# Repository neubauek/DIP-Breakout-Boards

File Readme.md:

# SMT to DIP Breakout Boards

Breakout boards to convert SMT chips to DIP format for use in breadboard prototyping.

These designs have all been validated against DirtyPCBs and OSHPark design rules, but most have not been panelized and sent off to be fabricated.

Be mindful of sizing when using QFN components. I noticed when developing my QFN-28 board that not all QFN-28 chips are created with equal footprints.

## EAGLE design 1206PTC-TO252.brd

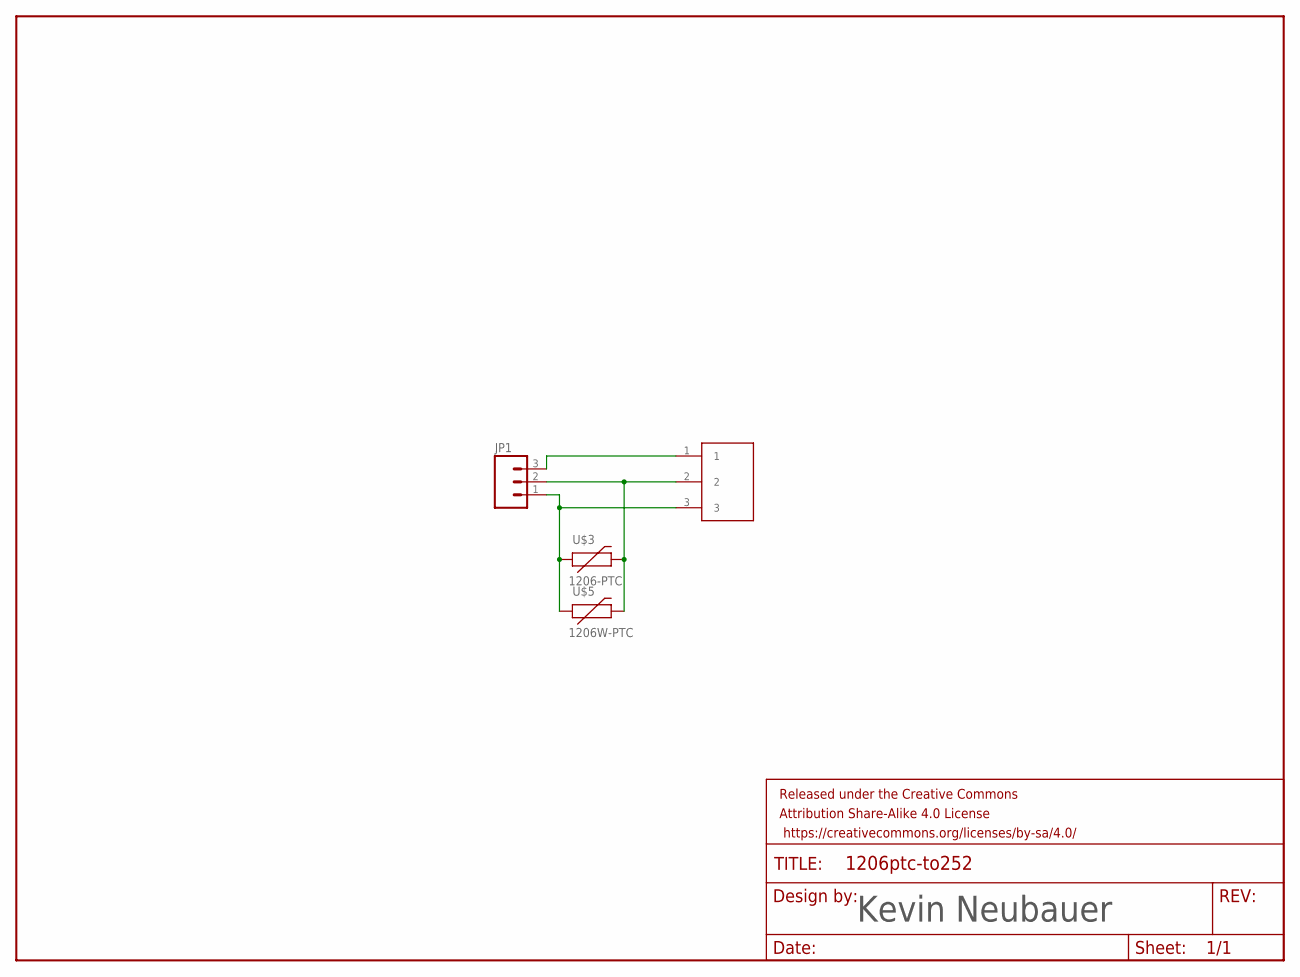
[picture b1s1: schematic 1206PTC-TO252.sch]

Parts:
FRAME1: FRAME-LETTER; CREATIVE_COMMONS
JP1: M03PTH; 1X03
U$3: 1206-PTC; PTC-1206
U$4: DPAK
U$5: 1206W-PTC; PTC-1206-WIDE

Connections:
unnamed: JP1.1, U$3.1, U$4.3, U$5.1
unnamed: JP1.2, U$3.2, U$4.2, U$5.2
unnamed: JP1.3, U$4.1

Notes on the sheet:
Kevin Neubauer

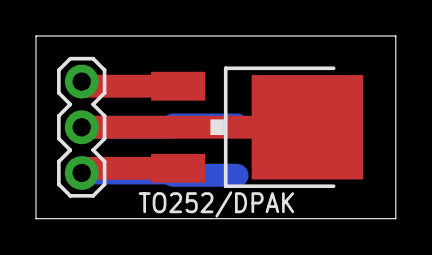
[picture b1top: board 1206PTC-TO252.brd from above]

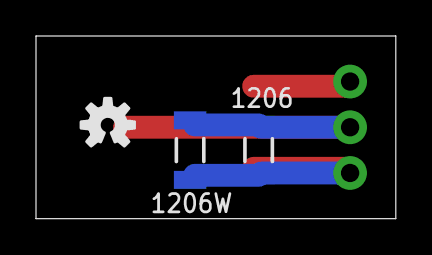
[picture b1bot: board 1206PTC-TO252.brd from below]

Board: 2 copper layers, 20.0 x 10.2 mm, 6 parts (3 on the bottom side), 3 nets.

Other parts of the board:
U$2: OSHW-LOGO-S

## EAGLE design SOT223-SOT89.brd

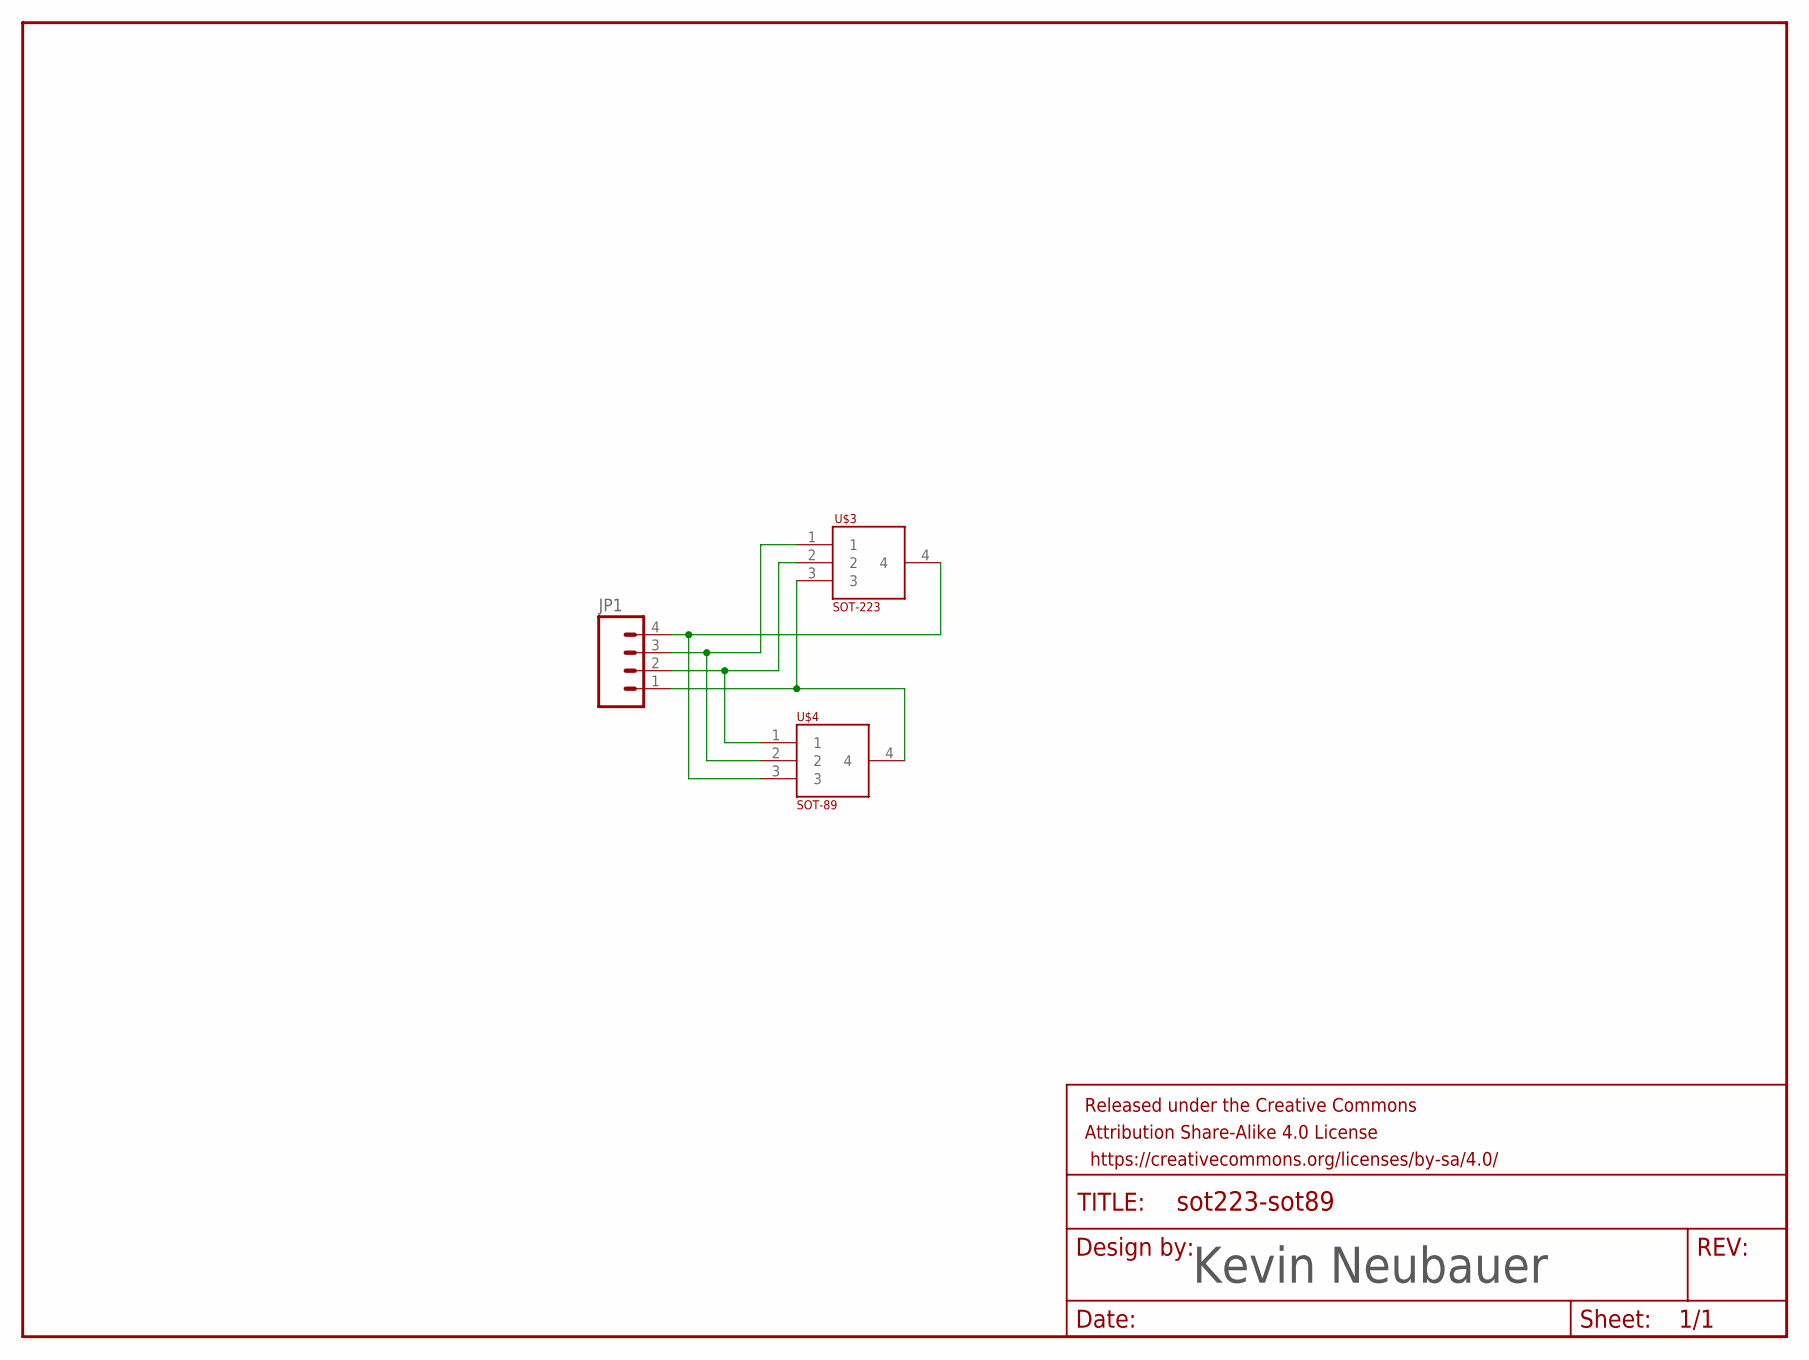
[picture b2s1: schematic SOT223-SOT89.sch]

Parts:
FRAME1: FRAME-LETTER; CREATIVE_COMMONS
JP1: M04PTH; 1X04
U$3: SOT-223
U$4: SOT-89

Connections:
unnamed: JP1.2, U$3.2, U$4.1
unnamed: JP1.3, U$3.1, U$4.2
unnamed: JP1.1, U$3.3, U$4.4
unnamed: JP1.4, U$3.4, U$4.3

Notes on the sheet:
Kevin Neubauer

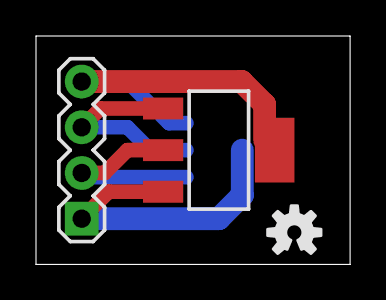
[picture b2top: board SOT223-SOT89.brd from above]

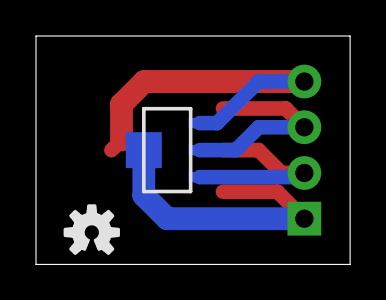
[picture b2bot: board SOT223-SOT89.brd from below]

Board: 2 copper layers, 17.5 x 12.7 mm, 6 parts (2 on the bottom side), 4 nets.

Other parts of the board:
U$1, U$2: OSHW-LOGO-S

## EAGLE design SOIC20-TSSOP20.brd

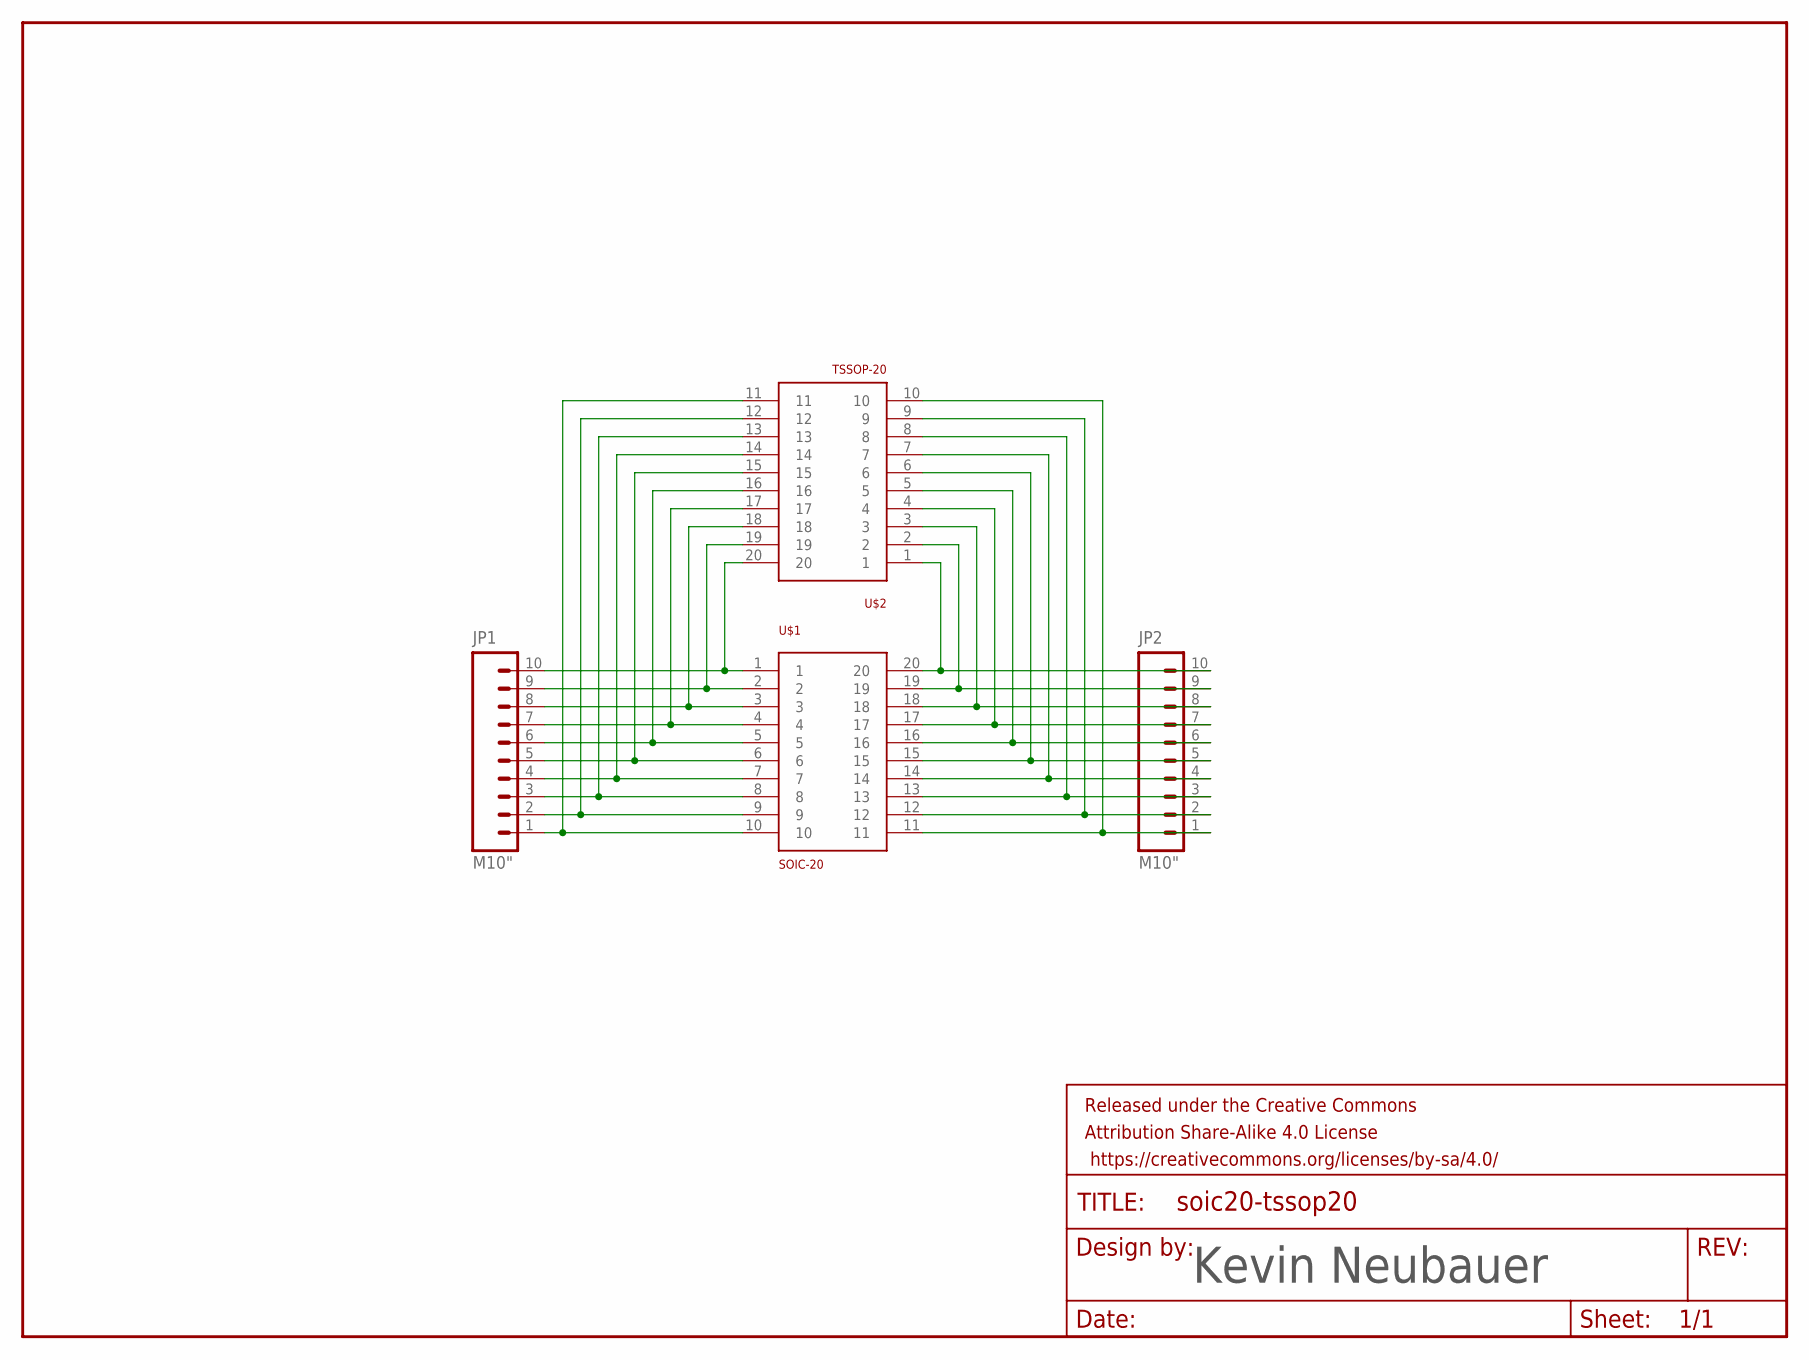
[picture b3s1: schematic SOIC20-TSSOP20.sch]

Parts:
FRAME1: FRAME-LETTER; CREATIVE_COMMONS
JP1, JP2: M10"; 1X10
U$1: SOIC-20
U$2: TSSOP-20; TSSOP20

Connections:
unnamed: JP1.10, U$1.1, U$2.20
unnamed: JP1.9, U$1.2, U$2.19
unnamed: JP1.8, U$1.3, U$2.18
unnamed: JP1.7, U$1.4, U$2.17
unnamed: JP1.6, U$1.5, U$2.16
unnamed: JP1.5, U$1.6, U$2.15
unnamed: JP1.4, U$1.7, U$2.14
unnamed: JP1.3, U$1.8, U$2.13
unnamed: JP1.2, U$1.9, U$2.12
unnamed: JP1.1, U$1.10, U$2.11
unnamed: JP2.10, U$1.20, U$2.1
unnamed: JP2.9, U$1.19, U$2.2
unnamed: JP2.8, U$1.18, U$2.3
unnamed: JP2.7, U$1.17, U$2.4
unnamed: JP2.6, U$1.16, U$2.5
unnamed: JP2.5, U$1.15, U$2.6
unnamed: JP2.4, U$1.14, U$2.7
unnamed: JP2.3, U$1.13, U$2.8
unnamed: JP2.2, U$1.12, U$2.9
unnamed: JP2.1, U$1.11, U$2.10

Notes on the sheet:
Kevin Neubauer

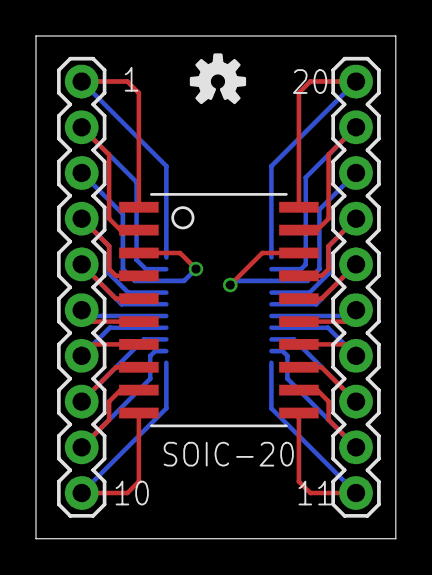
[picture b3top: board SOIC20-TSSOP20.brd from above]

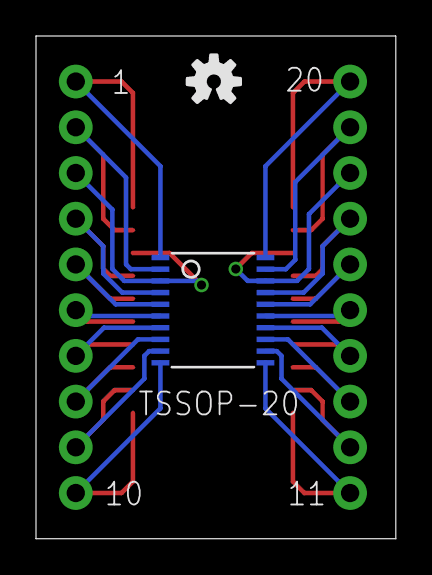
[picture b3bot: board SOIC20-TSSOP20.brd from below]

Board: 2 copper layers, 20.0 x 27.9 mm, 7 parts (2 on the bottom side), 20 nets.

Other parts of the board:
U$3, U$4: OSHW-LOGO-S

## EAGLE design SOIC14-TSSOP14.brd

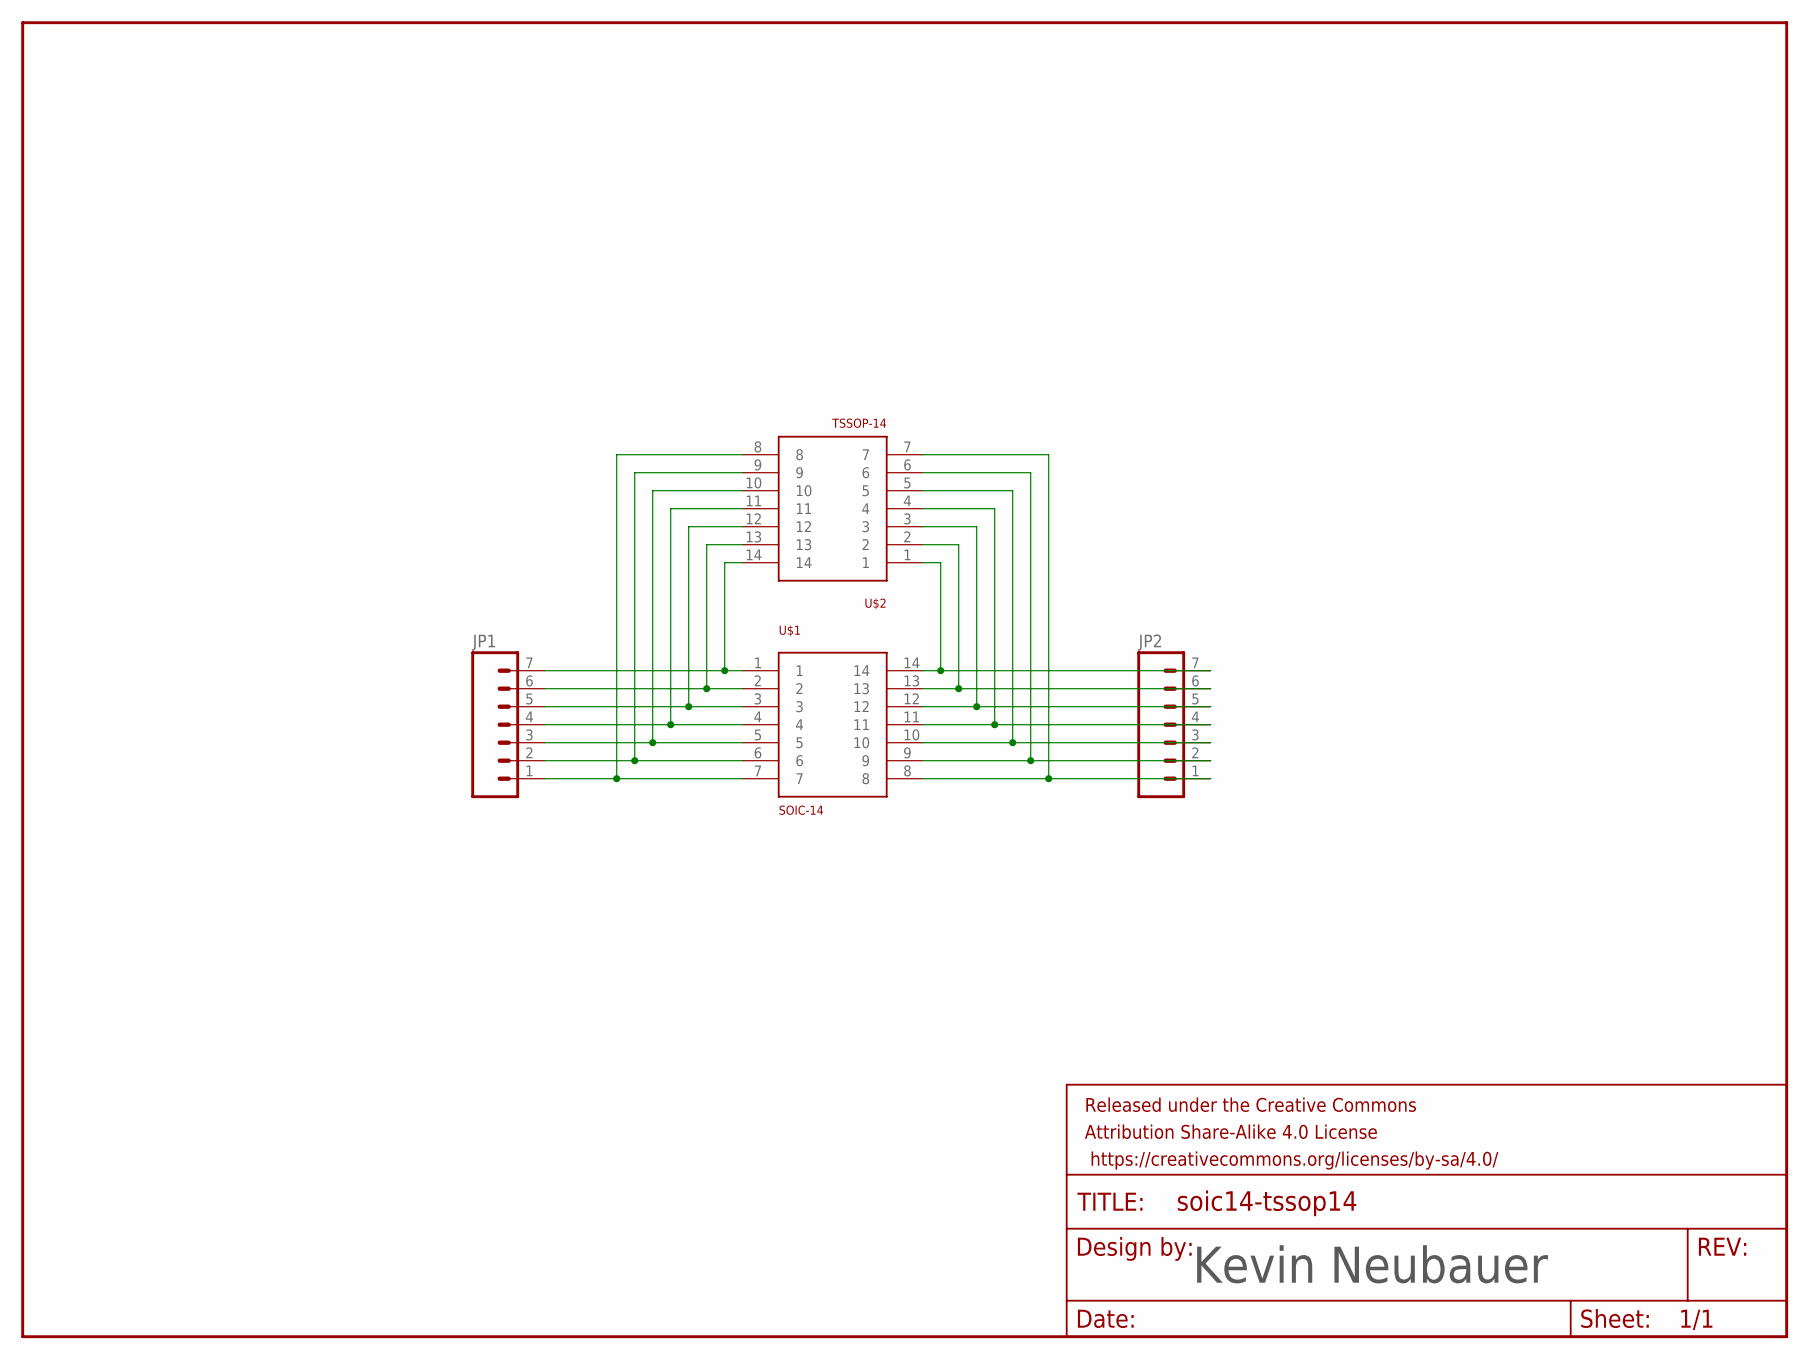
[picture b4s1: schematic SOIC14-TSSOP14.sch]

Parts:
FRAME1: FRAME-LETTER; CREATIVE_COMMONS
JP1, JP2: M07; 1X07
U$1: SOIC-14
U$2: TSSOP-14; TSSOP14

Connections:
unnamed: JP1.7, U$1.1, U$2.14
unnamed: JP1.6, U$1.2, U$2.13
unnamed: JP1.5, U$1.3, U$2.12
unnamed: JP1.4, U$1.4, U$2.11
unnamed: JP1.3, U$1.5, U$2.10
unnamed: JP1.2, U$1.6, U$2.9
unnamed: JP1.1, U$1.7, U$2.8
unnamed: JP2.7, U$1.14, U$2.1
unnamed: JP2.6, U$1.13, U$2.2
unnamed: JP2.5, U$1.12, U$2.3
unnamed: JP2.4, U$1.11, U$2.4
unnamed: JP2.3, U$1.10, U$2.5
unnamed: JP2.2, U$1.9, U$2.6
unnamed: JP2.1, U$1.8, U$2.7

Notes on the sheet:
Kevin Neubauer

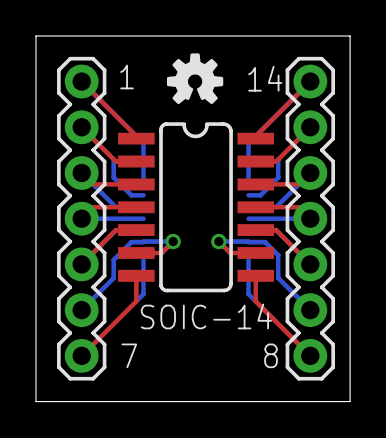
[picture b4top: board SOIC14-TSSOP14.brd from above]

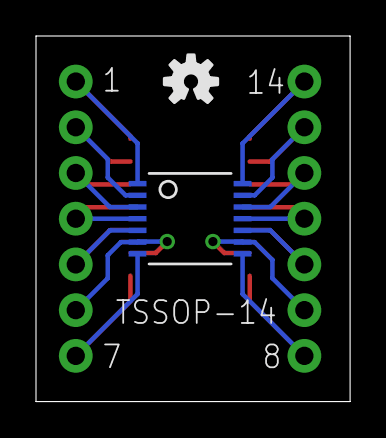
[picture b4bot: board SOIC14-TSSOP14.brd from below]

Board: 2 copper layers, 17.4 x 20.3 mm, 7 parts (2 on the bottom side), 14 nets.

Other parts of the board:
U$3, U$4: OSHW-LOGO-S

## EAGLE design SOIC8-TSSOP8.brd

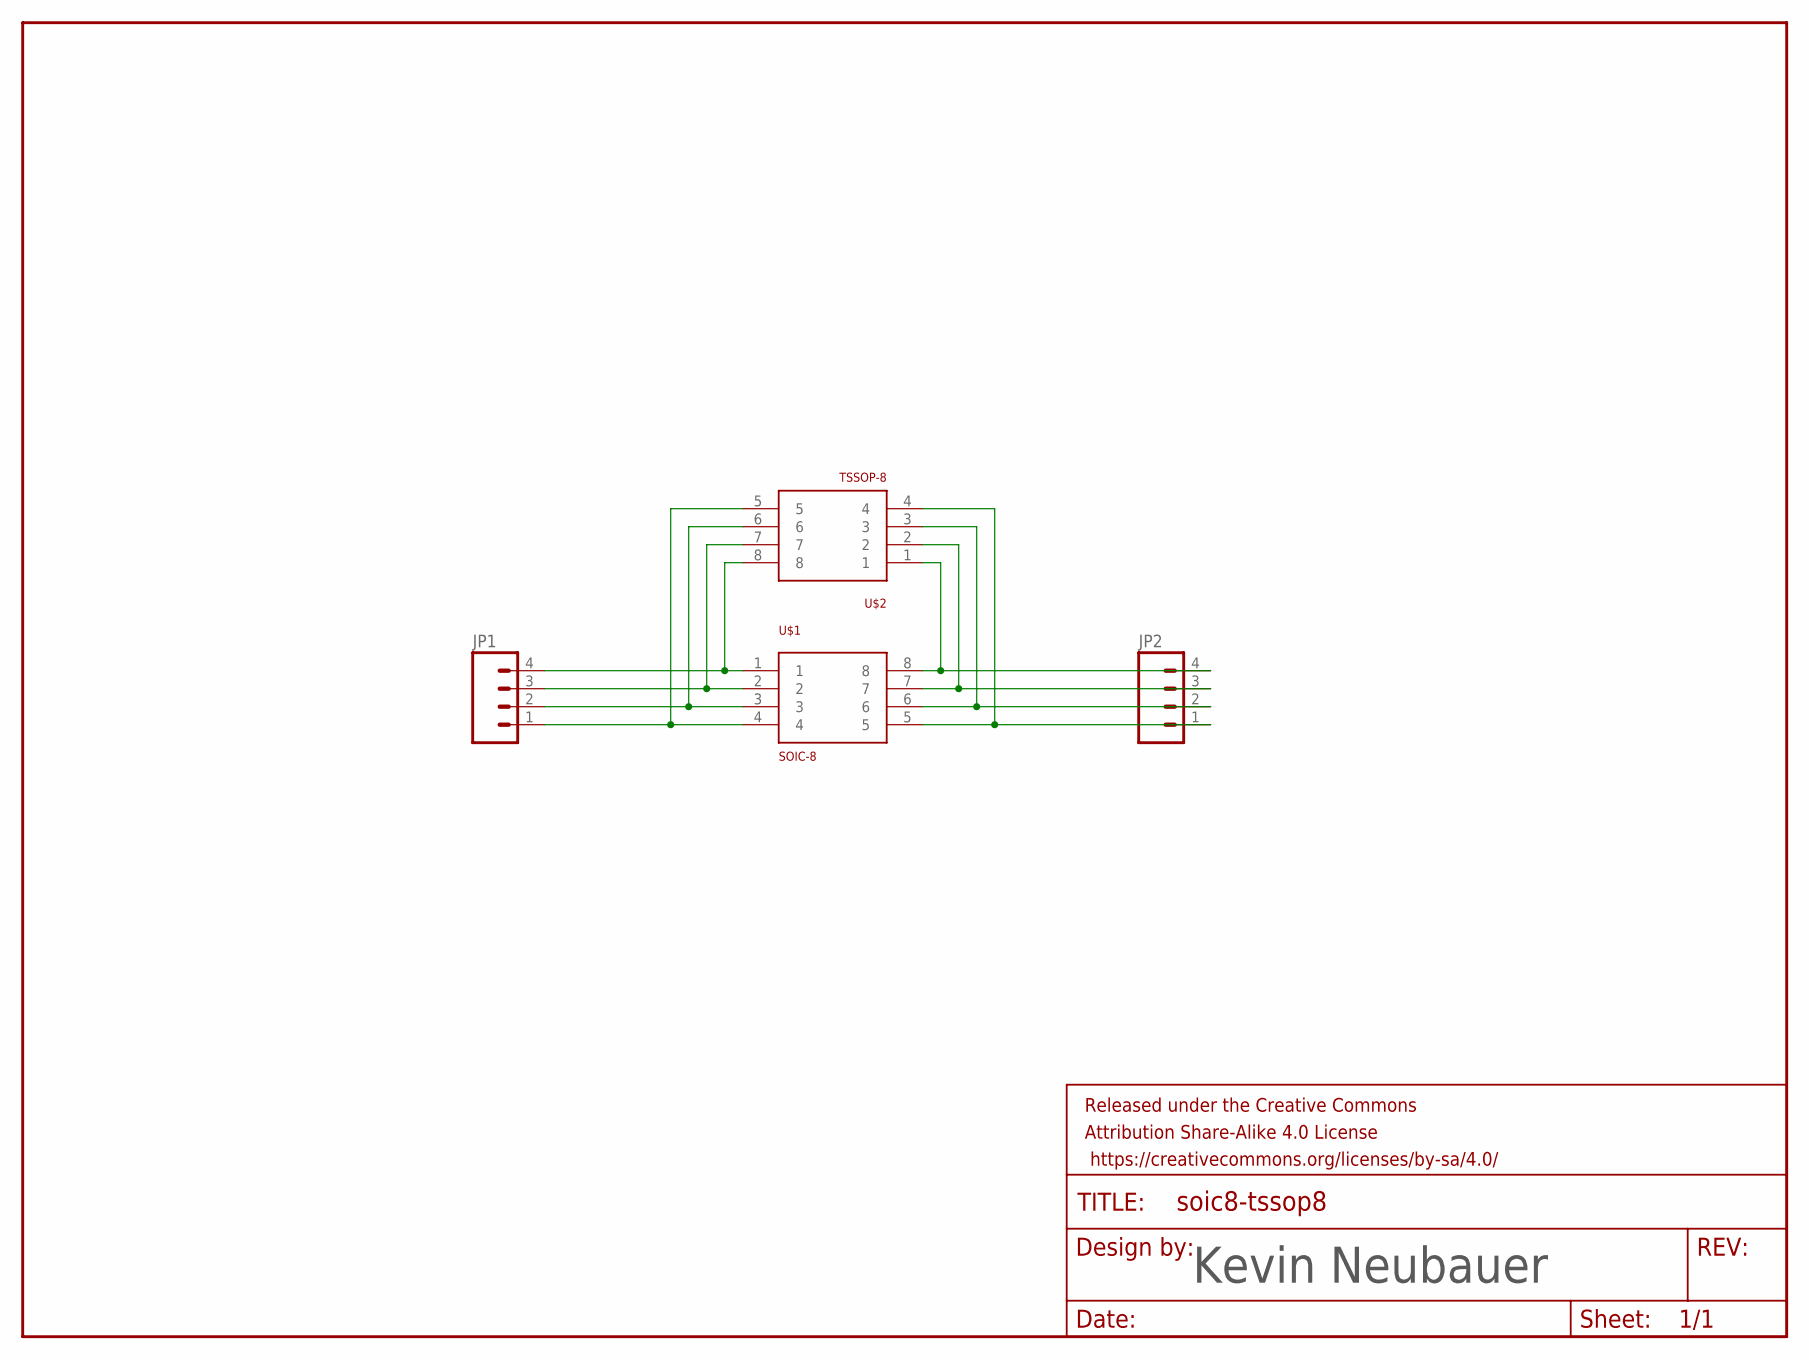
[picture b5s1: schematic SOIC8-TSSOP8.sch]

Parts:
FRAME1: FRAME-LETTER; CREATIVE_COMMONS
JP1, JP2: M04PTH; 1X04
U$1: SOIC-8
U$2: TSSOP-8; TSSOP8

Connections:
unnamed: JP1.4, U$1.1, U$2.8
unnamed: JP1.3, U$1.2, U$2.7
unnamed: JP1.2, U$1.3, U$2.6
unnamed: JP1.1, U$1.4, U$2.5
unnamed: JP2.4, U$1.8, U$2.1
unnamed: JP2.3, U$1.7, U$2.2
unnamed: JP2.2, U$1.6, U$2.3
unnamed: JP2.1, U$1.5, U$2.4

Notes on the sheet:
Kevin Neubauer

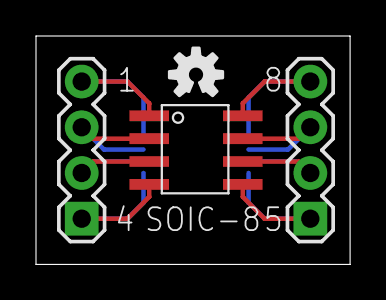
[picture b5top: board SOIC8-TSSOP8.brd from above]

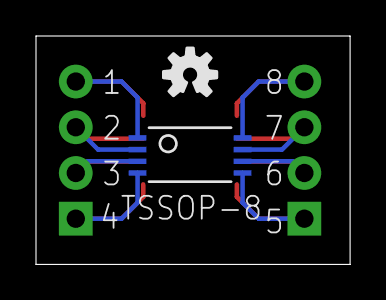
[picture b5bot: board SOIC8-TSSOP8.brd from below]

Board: 2 copper layers, 17.4 x 12.7 mm, 7 parts (2 on the bottom side), 8 nets.

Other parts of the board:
U$3, U$4: OSHW-LOGO-S

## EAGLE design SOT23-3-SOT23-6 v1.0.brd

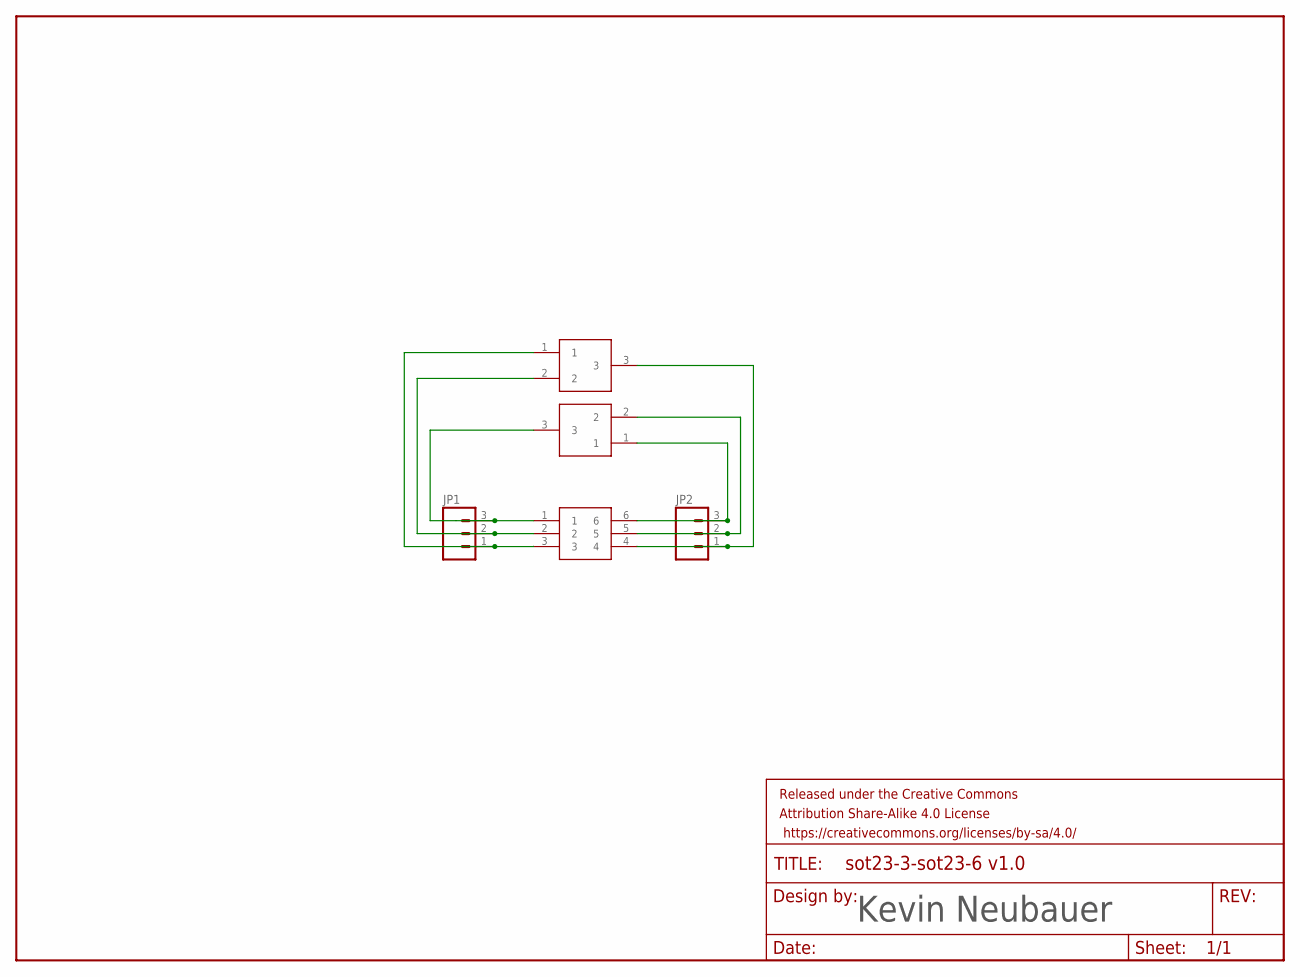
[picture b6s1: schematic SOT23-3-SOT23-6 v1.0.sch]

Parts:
FRAME1: FRAME-LETTER; CREATIVE_COMMONS
JP1, JP2: M03PTH; 1X03
U$3, U$4: SOT23-3
U$5: SOT23-6

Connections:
unnamed: JP1.2, U$3.2, U$5.2
unnamed: JP1.1, U$3.1, U$5.3
unnamed: JP2.3, U$4.1, U$5.6
unnamed: JP2.2, U$4.2, U$5.5
unnamed: JP2.1, U$3.3, U$5.4
unnamed: JP1.3, U$4.3, U$5.1

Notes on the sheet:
Kevin Neubauer

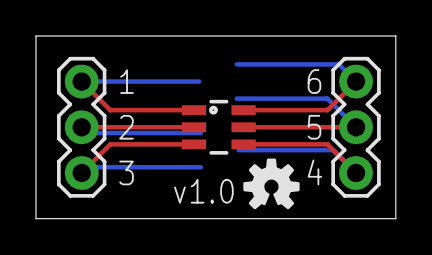
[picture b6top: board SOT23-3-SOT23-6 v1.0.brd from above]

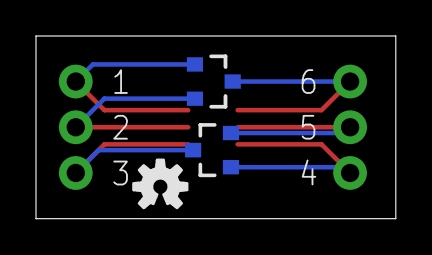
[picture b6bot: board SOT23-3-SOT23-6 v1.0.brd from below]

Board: 2 copper layers, 20.0 x 10.2 mm, 8 parts (3 on the bottom side), 6 nets.

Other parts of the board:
U$1, U$2: OSHW-LOGO-S

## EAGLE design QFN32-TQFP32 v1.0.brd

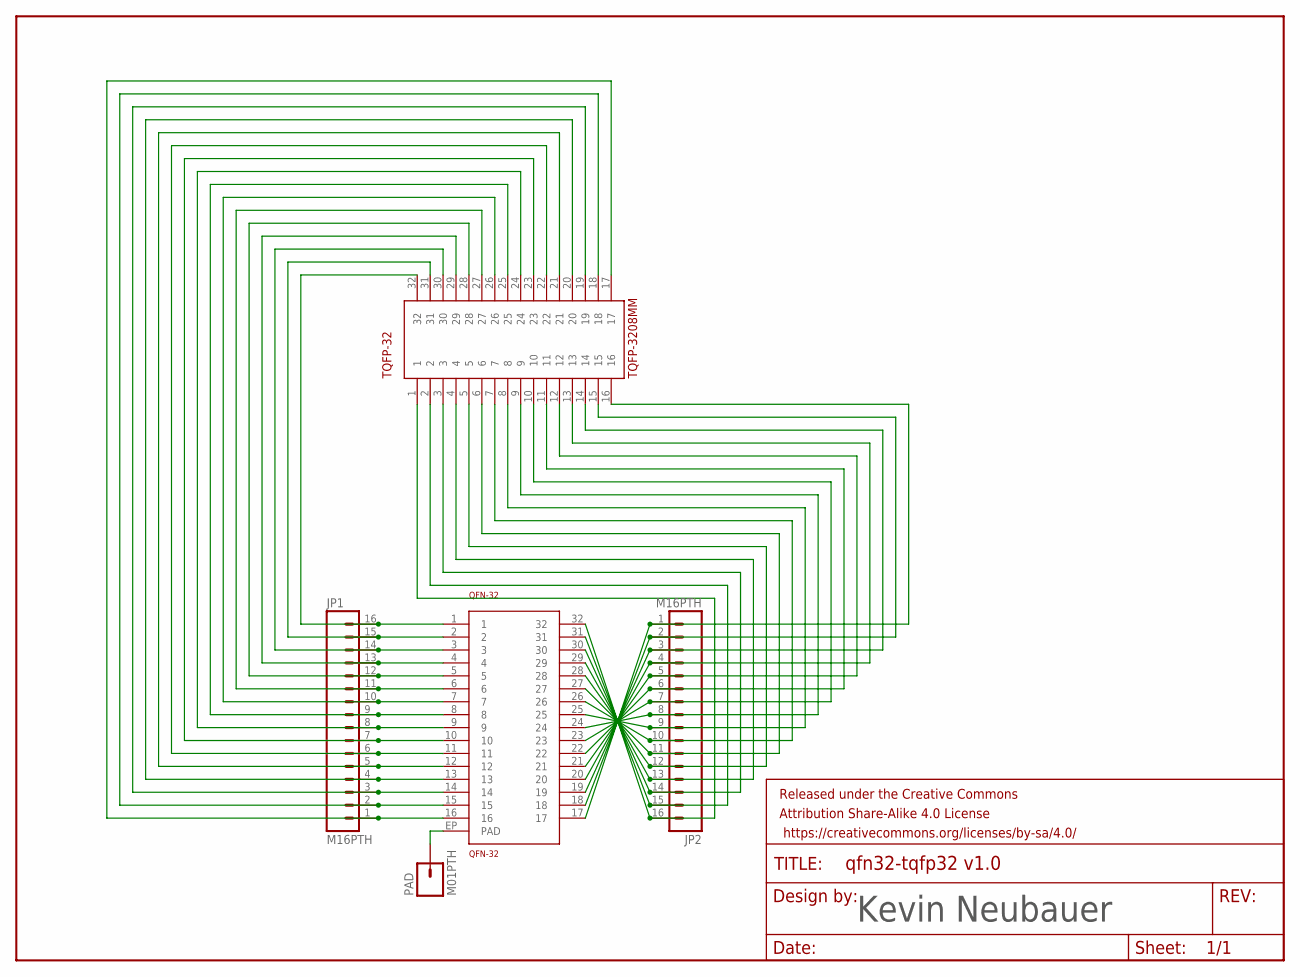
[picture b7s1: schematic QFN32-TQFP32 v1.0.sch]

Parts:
FRAME1: FRAME-LETTER; CREATIVE_COMMONS
JP1, JP2: M16PTH; 1X16
PAD: M01PTH; 1X01
QFN-32: QFN-32
TQFP-32: TQFP-3208MM; TQFP32-08

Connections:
GND: PAD.1, QFN-32.EP (PAD)
unnamed: JP2.9, QFN-32.25, TQFP-32.8
unnamed: JP1.16, QFN-32.1, TQFP-32.32
unnamed: JP1.15, QFN-32.2, TQFP-32.31
unnamed: JP1.14, QFN-32.3, TQFP-32.30
unnamed: JP1.13, QFN-32.4, TQFP-32.29
unnamed: JP1.11, QFN-32.6, TQFP-32.27
unnamed: JP1.10, QFN-32.7, TQFP-32.26
unnamed: JP1.9, QFN-32.8, TQFP-32.25
unnamed: JP1.8, QFN-32.9, TQFP-32.24
unnamed: JP1.7, QFN-32.10, TQFP-32.23
unnamed: JP1.6, QFN-32.11, TQFP-32.22
unnamed: JP1.5, QFN-32.12, TQFP-32.21
unnamed: JP1.4, QFN-32.13, TQFP-32.20
unnamed: JP1.3, QFN-32.14, TQFP-32.19
unnamed: JP1.2, QFN-32.15, TQFP-32.18
unnamed: JP1.1, QFN-32.16, TQFP-32.17
unnamed: JP2.14, QFN-32.30, TQFP-32.3
unnamed: JP2.13, QFN-32.29, TQFP-32.4
unnamed: JP2.12, QFN-32.28, TQFP-32.5
unnamed: JP2.11, QFN-32.27, TQFP-32.6
unnamed: JP2.10, QFN-32.26, TQFP-32.7
unnamed: JP2.2, QFN-32.18, TQFP-32.15
unnamed: JP2.8, QFN-32.24, TQFP-32.9
unnamed: JP2.7, QFN-32.23, TQFP-32.10
unnamed: JP2.5, QFN-32.21, TQFP-32.12
unnamed: JP2.4, QFN-32.20, TQFP-32.13
unnamed: JP2.3, QFN-32.19, TQFP-32.14
unnamed: JP2.15, QFN-32.31, TQFP-32.2
unnamed: JP2.16, QFN-32.32, TQFP-32.1
unnamed: JP2.1, QFN-32.17, TQFP-32.16
unnamed: JP1.12, QFN-32.5, TQFP-32.28
unnamed: JP2.6, QFN-32.22, TQFP-32.11

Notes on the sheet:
Kevin Neubauer

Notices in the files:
parts and their libraries:
Kevin-GenericICFootprints: Licensing: Creative Commons ShareAlike 4.0 International - https://creativecommons.org/licenses/by-sa/4.0
SparkFun-Aesthetics: Released under the Creative Commons Attribution Share-Alike 4.0 License
SparkFun-Aesthetics: https://creativecommons.org/licenses/by-sa/4.0
